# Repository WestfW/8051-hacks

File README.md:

# 8051-hacks
I have dabbled in some 8051/etc hardware designs.  Here they are!

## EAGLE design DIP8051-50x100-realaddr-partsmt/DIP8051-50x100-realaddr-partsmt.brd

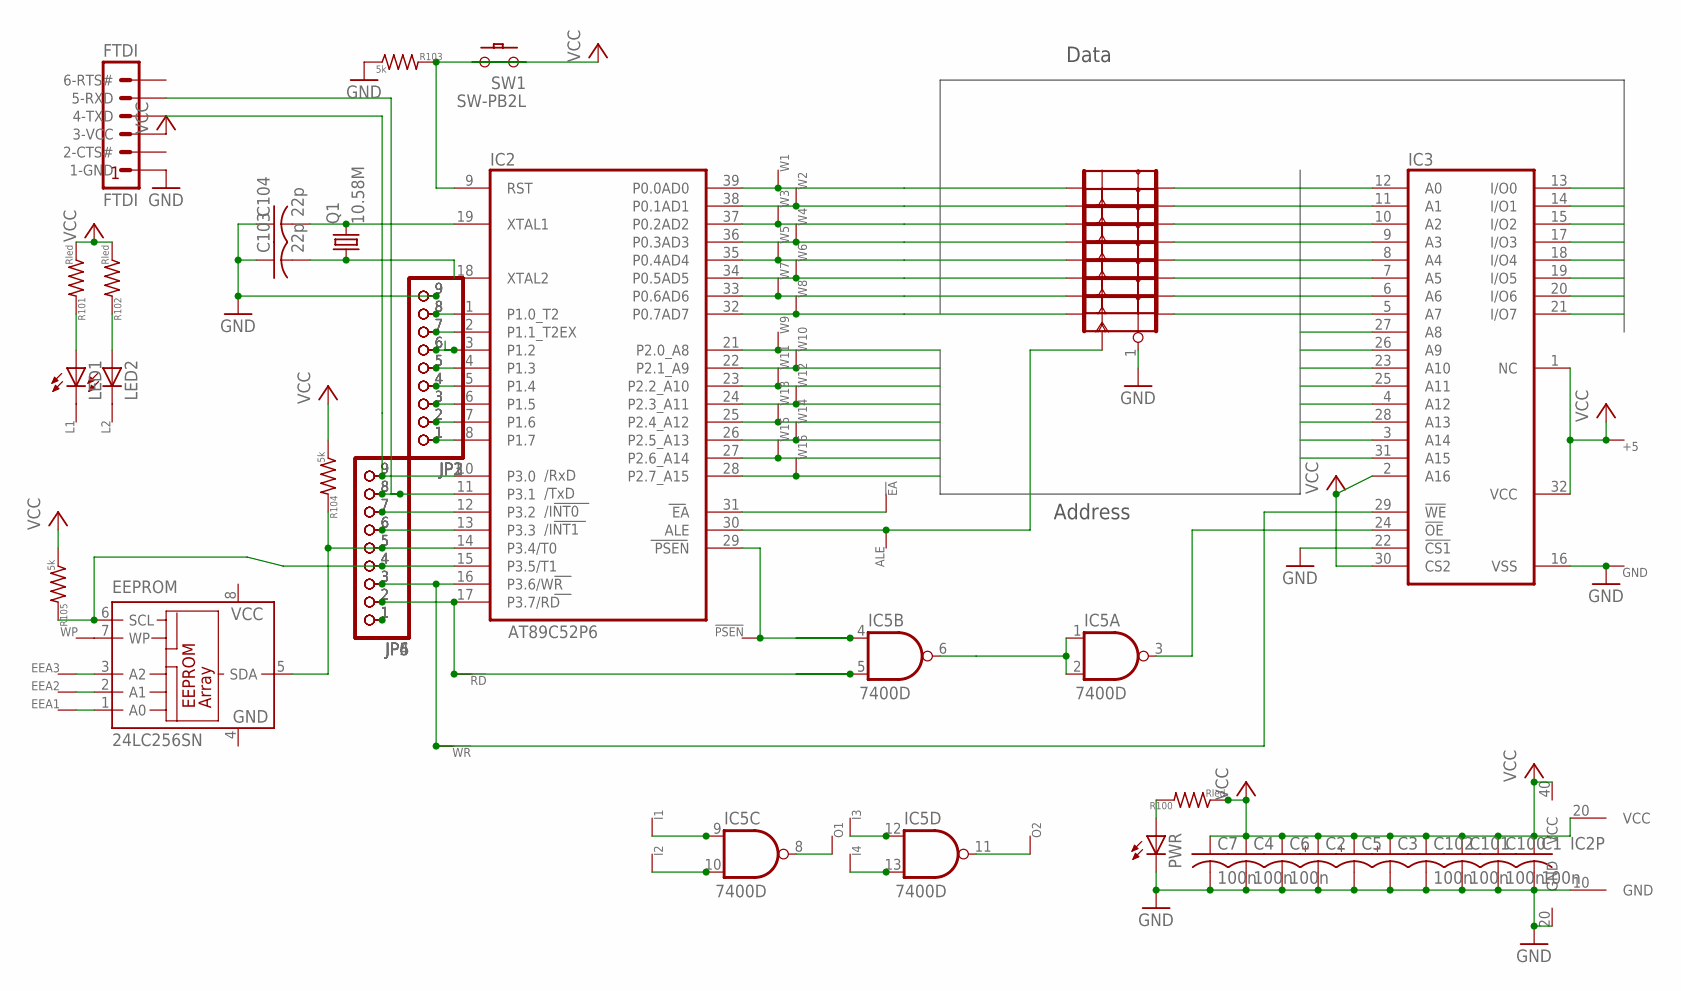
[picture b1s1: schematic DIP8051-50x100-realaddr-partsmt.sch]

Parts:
!EA: WIRE-R10; VIA10
!PSEN: WIRE-R10; VIA10
!RD: WIRE-R10; VIA10
!WR: WIRE-R10; VIA10
+5: WIRE-R12; VIA12
ALE: WIRE-R10; VIA10
C1, C6: 100n; C050-024X044
C2, C5: CPOL-US-C; SMC_C
C3: CPOL-USE2.5-7; E2,5-7
C4, C7, C100, C101, C102: 100n; C0805
C103, C104: 22p; C0805
EEA1, EEA2, EEA3: WIRE-R6; VIA6
EEPROM: 24LC256SN; SO-08
FTDI: FTDI; MA06-1
GND: WIRE-R12; VIA12
I1, I2, I3, I4: WIRE-VIA8; VIA8
IC1: 74573D; SO20W
IC2: AT89C52P6; DIL40
IC3: MEM128K-PS; DIL32
IC5: 7400D; SO14
JP1, JP2, JP3, JP4, JP5, JP6: PINHD-1X9; 1X09
L1, L2: WIRE-VIA8; VIA8
LED1, LED2: LED3MM
O1, O2: WIRE-VIA8; VIA8
PWR: LED3MM
Q1: 10.58M; HC49/S
R100, R101, R102: Rled; R0805
R103, R104, R105: 5k; R0805
SW1: SW-PB2L; SW-PB
W1, W2, W3, W4, W5, W6, W7, W8, W9, W10, W11, W12, W13, W14, W15, W16: WIRE-R10; VIA10
WP: WIRE-VIA8; VIA8

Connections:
!EA: !EA.P$1, IC2.31 (EA)
!OE: IC3.24 (!OE), IC5.3 (O)
!RD: !RD.P$1, IC2.17 (P3.7/RD), IC5.5 (I1), JP4.2, JP5.2, JP6.2
!WR: !WR.P$1, IC2.16 (P3.6/WR), IC3.29 (!WE), JP4.3, JP5.3, JP6.3
A0: IC1.19 (Q), IC3.12 (A0)
A1: IC1.18 (Q), IC3.11 (A1)
A2: IC1.17 (Q), IC3.10 (A2)
A3: IC1.16 (Q), IC3.9 (A3)
A4: IC1.15 (Q), IC3.8 (A4)
A5: IC1.14 (Q), IC3.7 (A5)
A6: IC1.13 (Q), IC3.6 (A6)
A7: IC1.12 (Q), IC3.5 (A7)
A8: IC2.21 (P2.0_A8), IC3.27 (A8), W9.P$1
A9: IC2.22 (P2.1_A9), IC3.26 (A9), W10.P$1
A10: IC2.23 (P2.2_A10), IC3.23 (A10), W11.P$1
A11: IC2.24 (P2.3_A11), IC3.25 (A11), W12.P$1
A12: IC2.25 (P2.4_A12), IC3.4 (A12), W13.P$1
A13: IC2.26 (P2.5_A13), IC3.28 (A13), W14.P$1
A14: IC2.27 (P2.6_A14), IC3.3 (A14), W15.P$1
A15: IC2.28 (P2.7_A15), IC3.31 (A15), W16.P$1
ALE: ALE.P$1, IC1.11 (CLK), IC2.30 (ALE)
D0: IC1.2 (D), IC2.39 (P0.0AD0), IC3.13 (I/O0), W1.P$1
D1: IC1.3 (D), IC2.38 (P0.1AD1), IC3.14 (I/O1), W2.P$1
D2: IC1.4 (D), IC2.37 (P0.2AD2), IC3.15 (I/O2), W3.P$1
D3: IC1.5 (D), IC2.36 (P0.3AD3), IC3.17 (I/O3), W4.P$1
D4: IC1.6 (D), IC2.35 (P0.4AD4), IC3.18 (I/O4), W5.P$1
D5: IC1.7 (D), IC2.34 (P0.5AD5), IC3.19 (I/O5), W6.P$1
D6: IC1.8 (D), IC2.33 (P0.6AD6), IC3.20 (I/O6), W7.P$1
D7: IC1.9 (D), IC2.32 (P0.7AD7), IC3.21 (I/O7), W8.P$1
GND: C1.2, C2.-, C3.-, C4.2, C5.-, C6.2, C7.2, C100.2, C101.2, C102.2, C103.1, C104.1, EEPROM.4 (GND), FTDI.1 (1-GND), GND.P$1, IC1.1 (OE), IC1.10 (GND), IC2.20 (GND), IC3.16 (VSS), IC3.22 (!CS1), IC5.7 (GND), JP1.9, JP2.9, JP3.9, PWR.K (C), R103.1, SW1.5 (GND)
unnamed: IC2.8 (P1.7), JP1.1, JP2.1, JP3.1
unnamed: EEA3.P$1, EEPROM.3 (A2)
unnamed: LED1.A, R101.2
unnamed: PWR.A, R100.2
unnamed: LED2.A, R102.2
unnamed: EEA2.P$1, EEPROM.2 (A1)
unnamed: EEA1.P$1, EEPROM.1 (A0)
unnamed: IC5.1 (I0), IC5.2 (I1), IC5.6 (O)
unnamed: IC2.7 (P1.6), JP1.2, JP2.2, JP3.2
unnamed: EEPROM.7 (WP), WP.P$1
unnamed: IC2.6 (P1.5), JP1.3, JP2.3, JP3.3
unnamed: IC2.5 (P1.4), JP1.4, JP2.4, JP3.4
unnamed: IC2.4 (P1.3), JP1.5, JP2.5, JP3.5
unnamed: IC2.2 (P1.1_T2EX), JP1.7, JP2.7, JP3.7
unnamed: C103.2, IC2.18 (XTAL2), Q1.1
unnamed: C104.2, IC2.19 (XTAL1), Q1.2
unnamed: IC2.1 (P1.0_T2), JP1.8, JP2.8, JP3.8
unnamed: IC2.12 (P3.2), JP4.7, JP5.7, JP6.7
unnamed: IC2.13 (P3.3), JP4.6, JP5.6, JP6.6
unnamed: !PSEN.P$1, IC2.29 (PSEN), IC5.4 (I0)
unnamed: I3.P$1, IC5.12 (I0)
unnamed: I4.P$1, IC5.13 (I1)
unnamed: IC5.11 (O), O2.P$1
unnamed: IC2.3 (P1.2), JP1.6, JP2.6, JP3.6
unnamed: I1.P$1, IC5.9 (I0)
unnamed: I2.P$1, IC5.10 (I1)
unnamed: IC5.8 (O), O1.P$1
unnamed: JP4.1, JP5.1, JP6.1
unnamed: L1.P$1, LED1.K (C)
unnamed: L2.P$1, LED2.K (C)
unnamed: IC2.9 (RST), R103.2, SW1.2
RXD: FTDI.4 (4-TXD), IC2.10 (P3.0), JP4.9, JP5.9, JP6.9
T0: EEPROM.5 (SDA), IC2.14 (P3.4/T0), JP4.5, JP5.5, JP6.5, R104.2
T1: EEPROM.6 (SCL), IC2.15 (P3.5/T1), JP4.4, JP5.4, JP6.4, R105.2
TXD: FTDI.5 (5-RXD), IC2.11 (P3.1), JP4.8, JP5.8, JP6.8
VCC: +5.P$1, C1.1, C2.+, C3.+, C4.1, C5.+, C6.1, C7.1, C100.1, C101.1, C102.1, EEPROM.8 (VCC), FTDI.3 (3-VCC), IC1.20 (VCC), IC2.40 (VCC), IC3.1 (NC), IC3.2 (A16), IC3.30 (CS2), IC3.32 (VCC), IC5.14 (VCC), R100.1, R101.1, R102.1, R104.1, R105.1, SW1.4

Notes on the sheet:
Address
Data

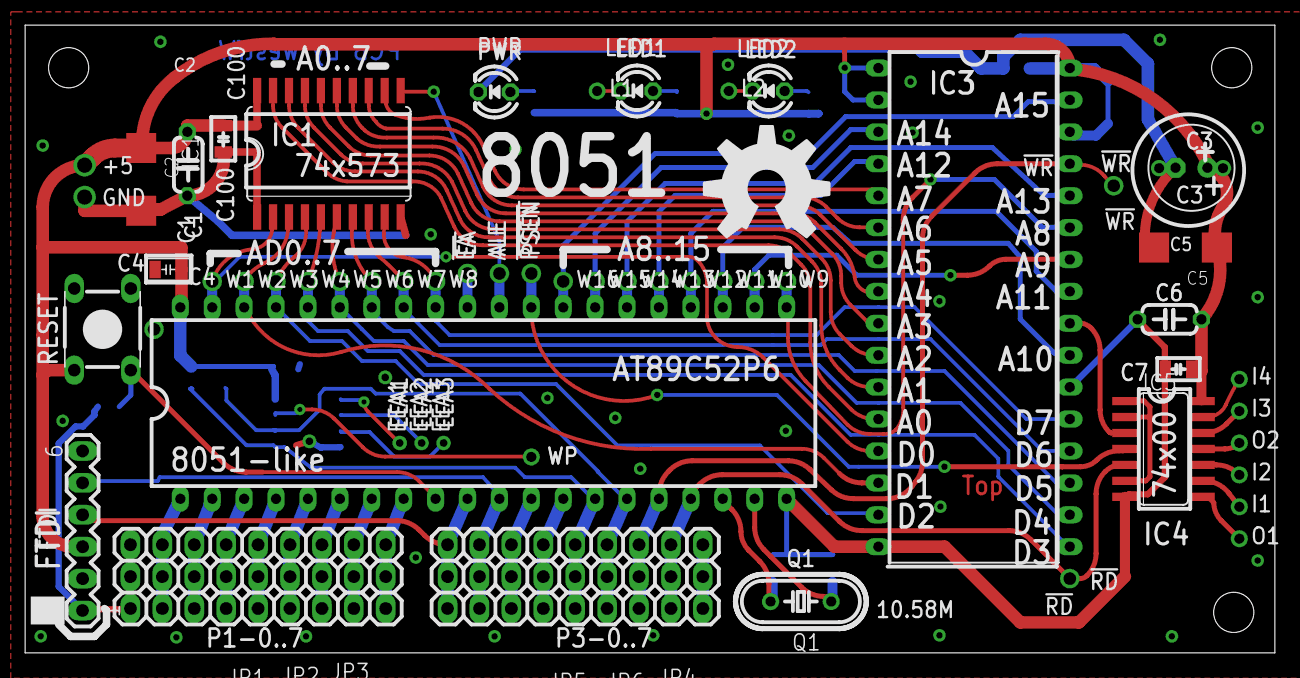
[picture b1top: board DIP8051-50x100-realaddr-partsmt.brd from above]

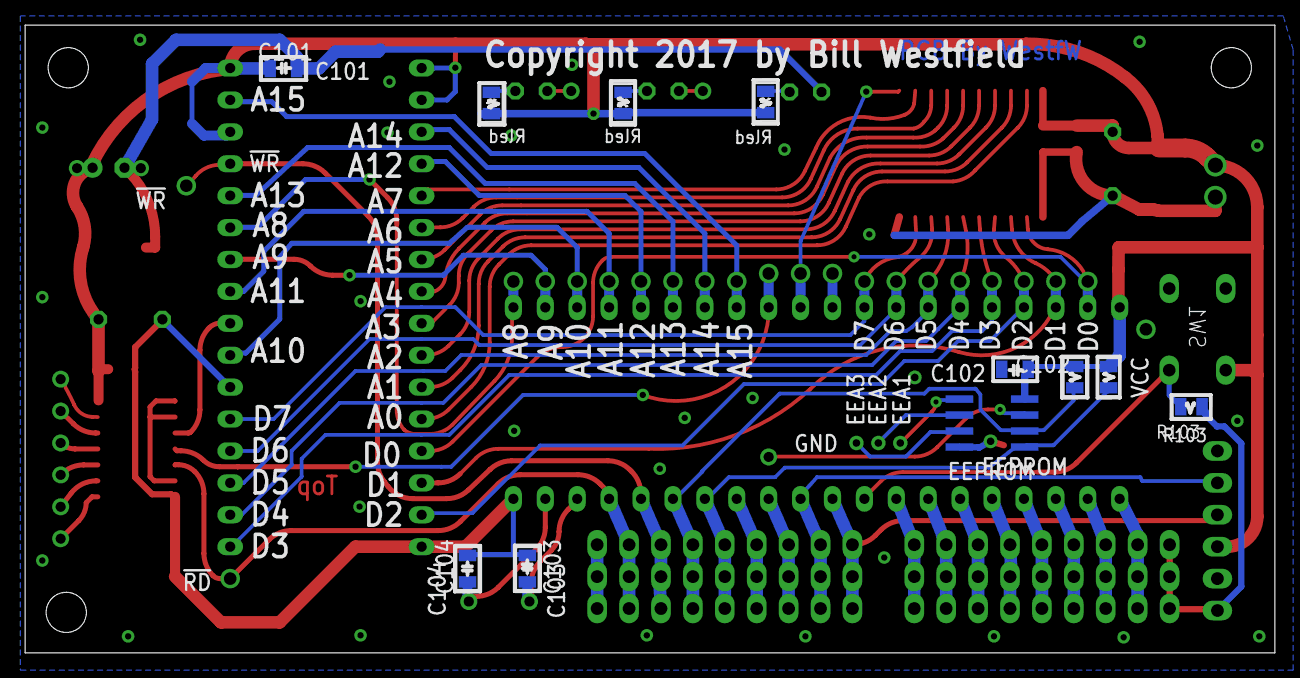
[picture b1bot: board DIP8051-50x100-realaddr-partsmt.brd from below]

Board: 2 copper layers, 99.5 x 50.0 mm, 70 parts (11 on the bottom side), 66 nets.

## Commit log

2026-05-28 Initial commit. EAGLE files; pdf of schematic, top and bottom pcb; and gerber files suitable for SeeedStudio

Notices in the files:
DIP8051-50x100-realaddr-partsmt/DIP8051-50x100-realaddr-partsmt.brd:
Copyright 2017 by Bill Westfield
